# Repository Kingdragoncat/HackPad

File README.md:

# HackPad 
This is a Github for all my hackpad files
## Components
### My HackPad Contains:
- Switches / buttons x5
- Rotary Encoder x1
- SK6812 Mini E RGB lights x11
- 0.91″ LCD Display
- Circuit Board
## Files Included
- BOM
- PCB
- Schematic
- Step
## Photos

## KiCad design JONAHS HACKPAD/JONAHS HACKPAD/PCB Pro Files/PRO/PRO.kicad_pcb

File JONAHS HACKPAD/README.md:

# HackPad — The Best Awesomeness HackPad of Doom and Awesomeness

Welcome to the Hack Club HackPad showcase for the HackPad project. This README gathers photos and board images so you can quickly see what the project looks like.

## Preview

Below are selected photos from the Fusion design exports and KiCad board/schematic images.

### Fusion Photos 

Assembled:

Case:

Lid:

### KiCad Photos (local PNGs)

Board render:

3D view:

Schematic:

## Files and folders

- Fusion exports and photos: [FUSION Photos](FUSION%20Photos)
- KiCad source and exports: [KICAD Files](KICAD%20Files)
- KiCad photos (local): [KICAD Photos](KICAD%20Photos)

.

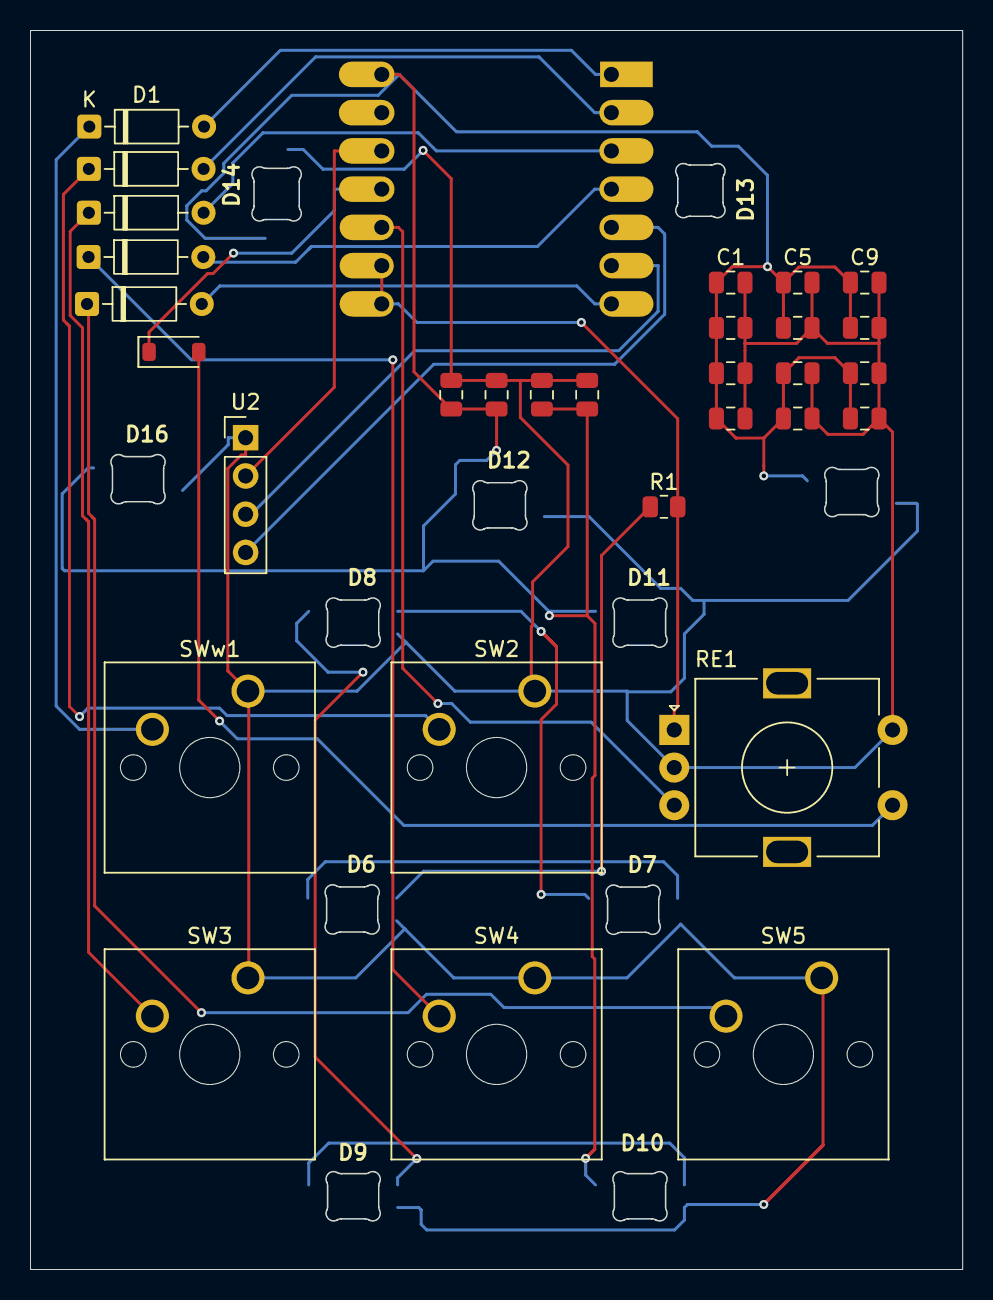
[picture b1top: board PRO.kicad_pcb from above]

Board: 2 copper layers, 61.9 x 82.3 mm, 42 parts (1 on the bottom side), 24 nets.

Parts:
C1, C2, C3, C4, C5, C6, C7, C8, C9, C10, C11, C12, C13, C14, C15: 100nF; C_0805_2012Metric
C16: 10uF; C_0805_2012Metric
D1, D2, D3, D4, D5: 1N4148; D_DO-35_SOD27_P7.62mm_Horizontal
D6, D7, D8, D9, D10, D11, D12, D13, D14, D15, D16: SK6812MINI-E; SK6812MINI-E_fixed
D17: 1N4148; D_SOD-123
R1: 470R; R_0805_2012Metric
RE1: RotaryEncoder_Switch; RotaryEncoder_Alps_EC11E-Switch_Vertical_H20mm
SW2, SW3, SW4, SW5: SW_Push; SW_Cherry_MX_1.00u_PCB
SWw1: SW_Push; SW_Cherry_MX_1.00u_PCB
U1: MOUDLE-SEEEDUINO-XIAO; XIAO-Generic-Hybrid-14P-2.54-21X17.8MM
U2: OLED_0.91_128x32; PinHeader_1x04_P2.54mm_Vertical

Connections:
GND: C1.2, C2.2, C3.2, C4.2, C5.2, C6.2, C7.2, C8.2, C9.2, C10.2, C11.2, C12.2, C13.2, C14.2, C15.2, C16.2, D6.3 (VSS), D7.3 (VSS), D8.3 (VSS), D9.3 (VSS), D10.3 (VSS), D11.3 (VSS), D12.3 (VSS), D14.3 (VSS), D15.3 (VSS), D16.3 (VSS), RE1.C, RE1.S2, SW2.1, SW3.1, SW4.1, SW5.1, SWw1.1, U2.1 (GND)
unnamed: D1.2 (A), U1.1 (PA02_A0_D0)
unnamed: D1.1 (K), SWw1.2
unnamed: D2.2 (A), U1.2 (PA4_A1_D1)
unnamed: D2.1 (K), SW2.2
unnamed: D3.2 (A), U1.3 (PA10_A2_D2)
unnamed: D3.1 (K), SW3.2
unnamed: D4.2 (A), U1.4 (PA11_A3_D3)
unnamed: D4.1 (K), SW4.2
unnamed: D5.2 (A), U1.7 (PB08_A6_D6_TX)
unnamed: D5.1 (K), SW5.2
unnamed: D6.4 (DIN), R1.1
unnamed: D6.1 (DOUT), D7.4 (DIN)
unnamed: D7.1 (DOUT), D8.4 (DIN)
unnamed: D8.1 (DOUT), D9.4 (DIN)
unnamed: D9.1 (DOUT), D10.4 (DIN)
unnamed: C1.1, C2.1, C3.1, C4.1, C5.1, C6.1, C7.1, C8.1, C9.1, C10.1, C11.1, C12.1, C13.1, C14.1, C15.1, C16.1, D10.1 (VDD), D11.1 (VDD), D12.1 (VDD), D13.1 (VDD), D14.1 (VDD), D15.1 (VDD), D16.1 (VDD), U1.14 (5V)
unnamed: D17.2 (A), RE1.S1
unnamed: D17.1 (K), U1.11 (PA6_A10_D10_MOSI)
unnamed: U1.12 (3V3), U2.2 (VCC)
unnamed: RE1.B, U1.10 (PA5_A9_D9_MISO)
unnamed: R1.2, RE1.A, U1.8 (PB09_A7_D7_RX), U1.9 (PA7_A8_D8_SCK)
unnamed: U1.5 (PA8_A4_D4_SDA), U2.4 (SDA)
unnamed: U1.6 (PA9_A5_D5_SCL), U2.3 (SCL)

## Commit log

2026-01-31 Initial Hackpad Commit of doom!
2026-01-31 Initial plan
2026-01-31 Add comprehensive README for HackPad project
2026-01-31 Initialize README with HackPad project details
    Added detailed information about the HackPad project, including components, files included, and photos.
2026-01-31 Add initial firmware for LED and encoder control
2026-01-31 update stuff
2026-03-10 proper v1.3 files
2026-03-10 updated photos
2026-03-10 Add README, download KiCad images (use local PNGs)
2026-03-10 Fix README image paths: encode spaces for GitHub
2026-03-10 Fix README folder links: encode spaces
2026-03-13 move stuff to root cad and diode fix
2026-03-13 Flatten project layout: move HackPad files to repo root
